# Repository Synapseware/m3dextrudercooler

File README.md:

M3D Pro and Micro Extruder Cooler
=================================

## About
The M3D Pro (and micro to some extent) suffer from some really terrible design decisions.  For example, after printer for about 15-20 minutes on the Pro, the extruder usually heats up enough to melt the filament, which of course causes the print to fail and the extruder gear to get all jammed up with melted filament.

This cooler aims to solve that by monitoring the temperature at or near the extruder gear and directing a fan to blow more or less depending on how hot it is.

# MCU
The controlling chip is an ATTiny25/45/85 running around 8MHz and driven from a 5V supply (using a USB-wall wort, LM7805, etc.).

## ADC Input
The cooler samples the ADC input every 10 seconds or so, and ramps up fan speed based on temperature.

### ADC Input Pin
The ADC is configured to read from pin PB3.

### ADC Sense Line
The input to the ADC should be constrained to 0.0v through 1.1v.  This gives the most accuracy on the ADC and allows for a small load/sense resistor.

## PWM Output
Timer1 is used to generate the PWM signal that drives the MOSFET which is connected to the motor.  The switching frequency is set for best performance with the given fan, and will need to be tuned in firmware.

### PWM Output Pin
The PWM output is available on PB1.  The output should not be filtered since it must be fed to the MOSFET switch.  Care should be taken to keep this line short and include an appropriately sized pull-down resistor to ensure safe operation of the power MOSFET or other switching transistor.

## Other Chip Information
The AVR uC is configured to use it's internal R/C oscillator.  High clock accuracy is not needed by this circuit and keeping the part count low is a goal of this example.

## Build
This project compiles and uploads just fine using Linux and avr-gnu.

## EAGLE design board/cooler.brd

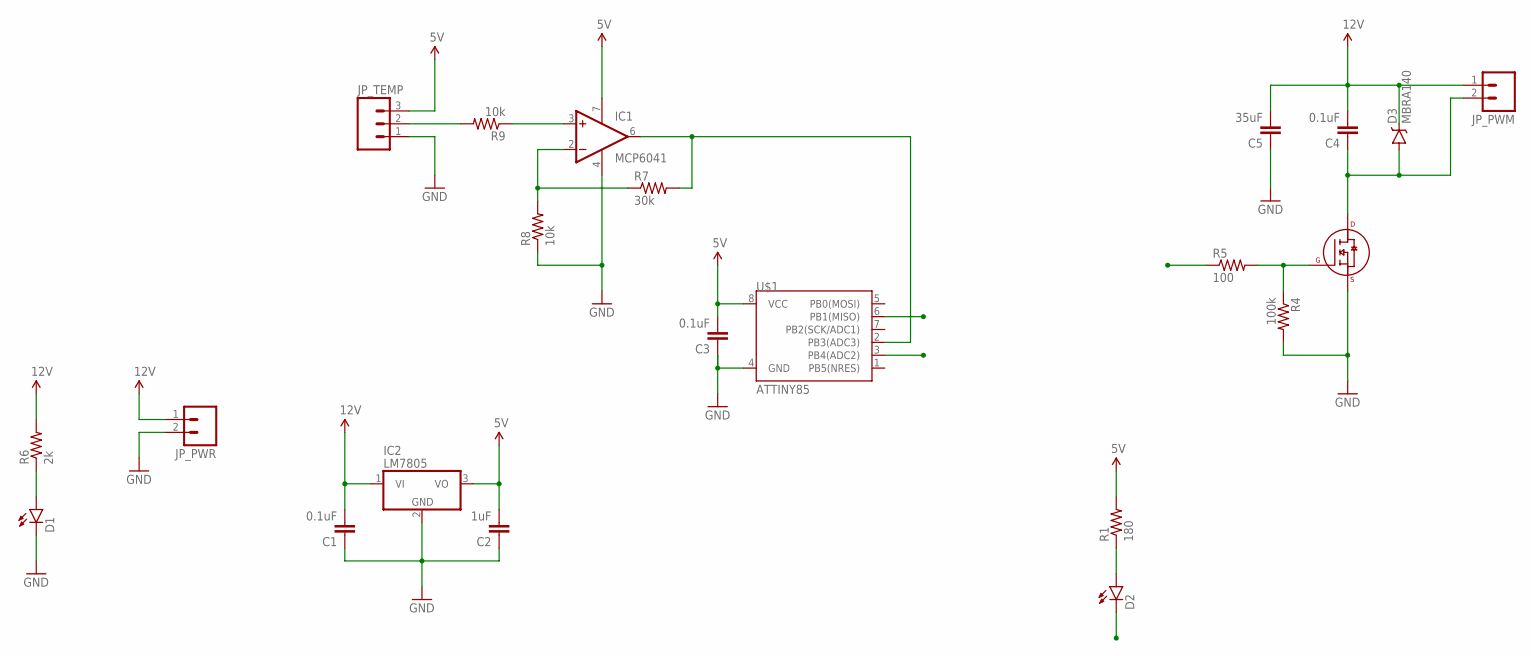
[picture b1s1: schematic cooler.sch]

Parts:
C1, C3, C4: 0.1uF; 1210
C2: 1uF; 1210
C5: 35uF; 1210
D1, D2: LED1206; LED-1206
D3: MBRA140; SMA-DIODE
IC1: MCP6041; SO08
IC2: LM7805; TO220V
JP_PWM: M02LOCK_LONGPADS; 1X02_LOCK_LONGPADS
JP_PWR: M02LOCK_LONGPADS; 1X02_LOCK_LONGPADS
JP_TEMP: M03LONGPADS; 1X03_LONGPADS
Q2: 2N7000-2SOT-23; SOT-23-3
R1: 180; R2010
R4: 100k; R2010
R5: 100; R2010
R6: 2k; R2010
R7: 30k; R2010
R8, R9: 10k; R2010
U$1: ATTINY85; SO08

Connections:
5V: C2.2, C3.2, IC1.7 (V+), IC2.3 (VO), JP_TEMP.3, R1.2, U$1.8 (VCC)
12V: C1.2, C4.2, C5.2, D3.C, IC2.1 (VI), JP_PWM.1, JP_PWR.1, R6.2
ADC_IN: IC1.6 (OUT), R7.2, U$1.2 (PB3(ADC3))
GND: C1.1, C2.1, C3.1, C5.1, D1.C, IC1.4 (V-), IC2.2 (GND), JP_PWR.2, JP_TEMP.1, Q2.2 (S), R4.2, R8.1, U$1.4 (GND)
LED: D2.C, U$1.3 (PB4(ADC2))
unnamed: Q2.1 (G), R4.1, R5.2
unnamed: D1.A, R6.1
unnamed: IC1.3 (+IN), R9.1
unnamed: IC1.2 (-IN), R7.1, R8.2
unnamed: D2.A, R1.1
unnamed: C4.1, D3.A, JP_PWM.2, Q2.3 (D)
PWM: R5.1, U$1.6 (PB1(MISO))
TMP_IN: JP_TEMP.2, R9.2

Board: 2 copper layers, 22 parts (0 on the bottom side), 13 nets, no tracks yet.

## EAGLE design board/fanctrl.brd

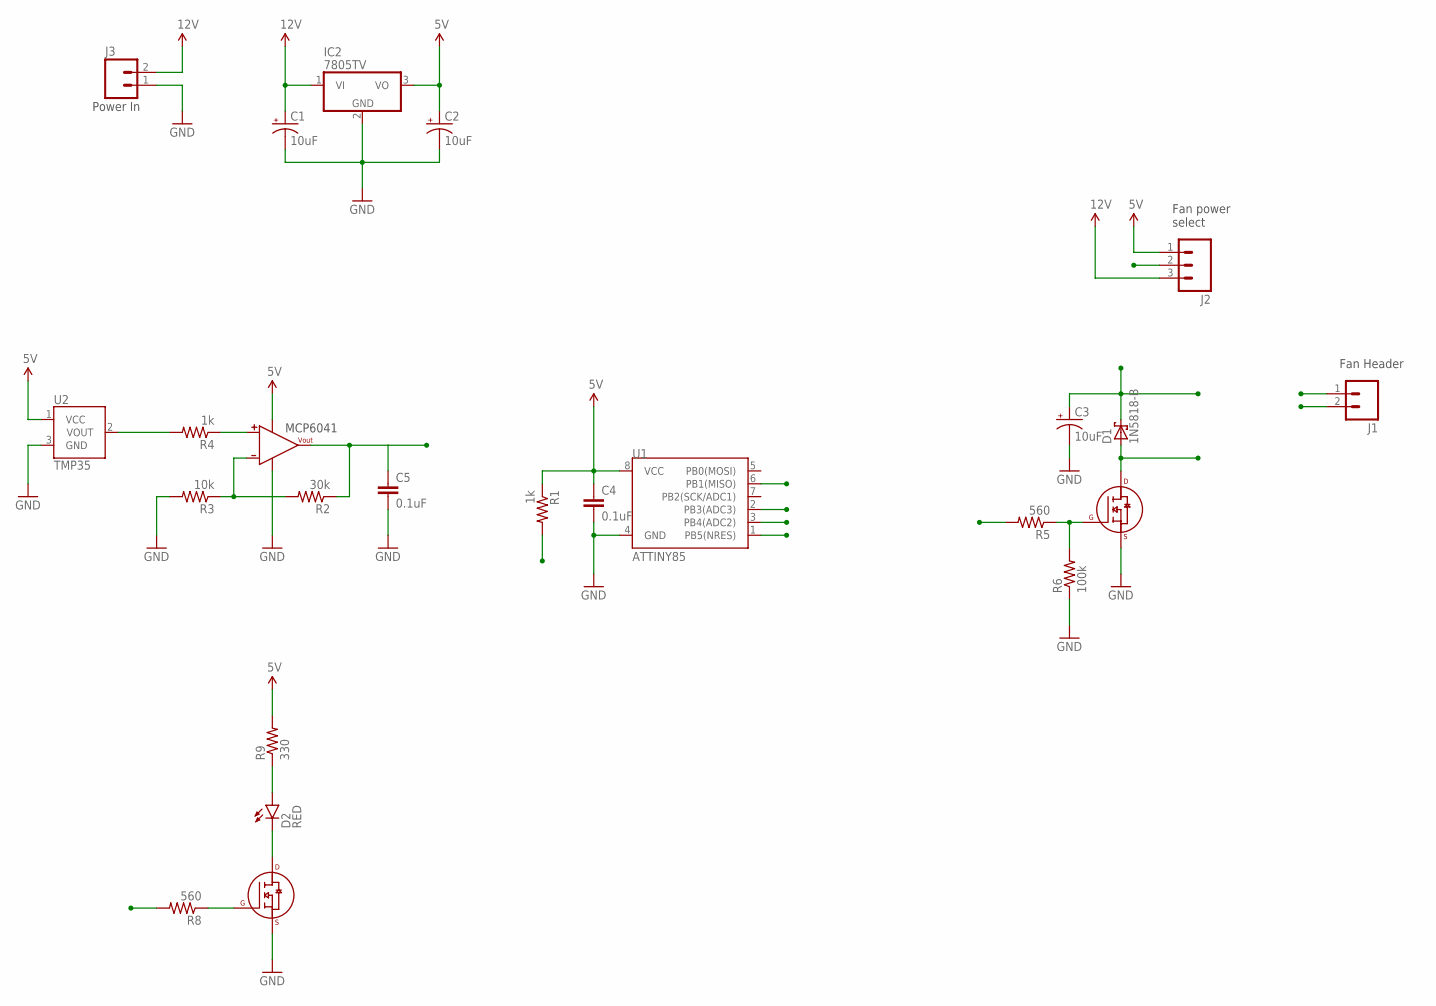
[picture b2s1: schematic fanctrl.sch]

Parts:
C1, C2, C3: 10uF; CPOL-RADIAL-10UF-25V
C4, C5: 0.1uF; CAP-PTH-SMALLEZ
D1: 1N5818-B; DO41-7.6
D2: RED; LED5MM
IC2: 7805TV; TO220V
J1: M02JST-PTH-VERT; JST-2-PTH-VERT
J2: M03PTH; 1X03
J3: M02PTH; 1X02
MCP6041: MCP6041DIP; PDIP-8
R1, R4: 1k; AXIAL-0.1
R2: 30k; AXIAL-0.1
R3: 10k; AXIAL-0.1
R5, R8: 560; AXIAL-0.1
R6: 100k; AXIAL-0.1
R9: 330; AXIAL-0.1
U1: ATTINY85; DIP08
U2: TMP35; TO-92
U$1, U$2: 2N7000; TO-92

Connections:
5V: C2.1 (+), C4.1, IC2.3 (VO), J2.1, MCP6041.7 (VDD), R1.P$1 (1), R9.P$2 (2), U1.8 (VCC), U2.1 (VCC)
12V: C1.1 (+), IC2.1 (VI), J2.3, J3.2
/RESET: R1.P$2 (2), U1.1 (PB5(NRES))
FAN_POWER: C3.1 (+), D1.C, J1.1, J2.2
GND: C1.2 (-), C2.2 (-), C3.2 (-), C4.2, C5.2, IC2.2 (GND), J3.1, MCP6041.4 (VSS), R3.P$2 (2), R6.P$1 (1), U1.4 (GND), U2.3 (GND), U$1.3 (S), U$2.3 (S)
LED: R8.P$2 (2), U1.3 (PB4(ADC2))
MOTOR-: D1.A, J1.2, U$1.1 (D)
unnamed: R4.P$2 (2), U2.2 (VOUT)
unnamed: MCP6041.2 (-), R2.P$2 (2), R3.P$1 (1)
unnamed: R5.P$1 (1), R6.P$2 (2), U$1.2 (G)
unnamed: MCP6041.3 (+), R4.P$1 (1)
unnamed: D2.A, R9.P$1 (1)
unnamed: D2.K (C), U$2.1 (D)
unnamed: R8.P$1 (1), U$2.2 (G)
PWM: R5.P$2 (2), U1.6 (PB1(MISO))
SENSOR: C5.1, MCP6041.6 (VOUT), R2.P$1 (1), U1.2 (PB3(ADC3))

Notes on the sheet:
MCP6041
Fan power select
Power In
Fan Header

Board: 2 copper layers, 24 parts (0 on the bottom side), 16 nets, no tracks yet.

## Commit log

2018-06-04 Hardware setup is complete but untested
2018-06-04 Initial state machine processing
    Smartly run the fans by forcing a cool-down period, after which the fan
    can speed up, but not speed down until the temp of the extruder starts
    to fall.
2018-06-07 Use board file for hardware config
2018-06-07 Timers working, motor control non-functional
2018-06-07 Transfer functions are working
2018-06-08 Adding simple teset program
2018-06-08 Transfer function updated
2018-06-08 Test cleanup
2018-06-11 Use event system and convert to cpp
2018-06-12 Makefile update - remove transient files
2018-06-17 Misc formatting
2018-06-17 Use a parabolic function for fan speed
2018-07-29 Added circuit schematic
2019-09-23 Cooler control board

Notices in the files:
parts and their libraries:
SparkFun-Capacitors: Licensing: Creative Commons ShareAlike 4.0 International - https://creativecommons.org/licenses/by-sa/4.0
